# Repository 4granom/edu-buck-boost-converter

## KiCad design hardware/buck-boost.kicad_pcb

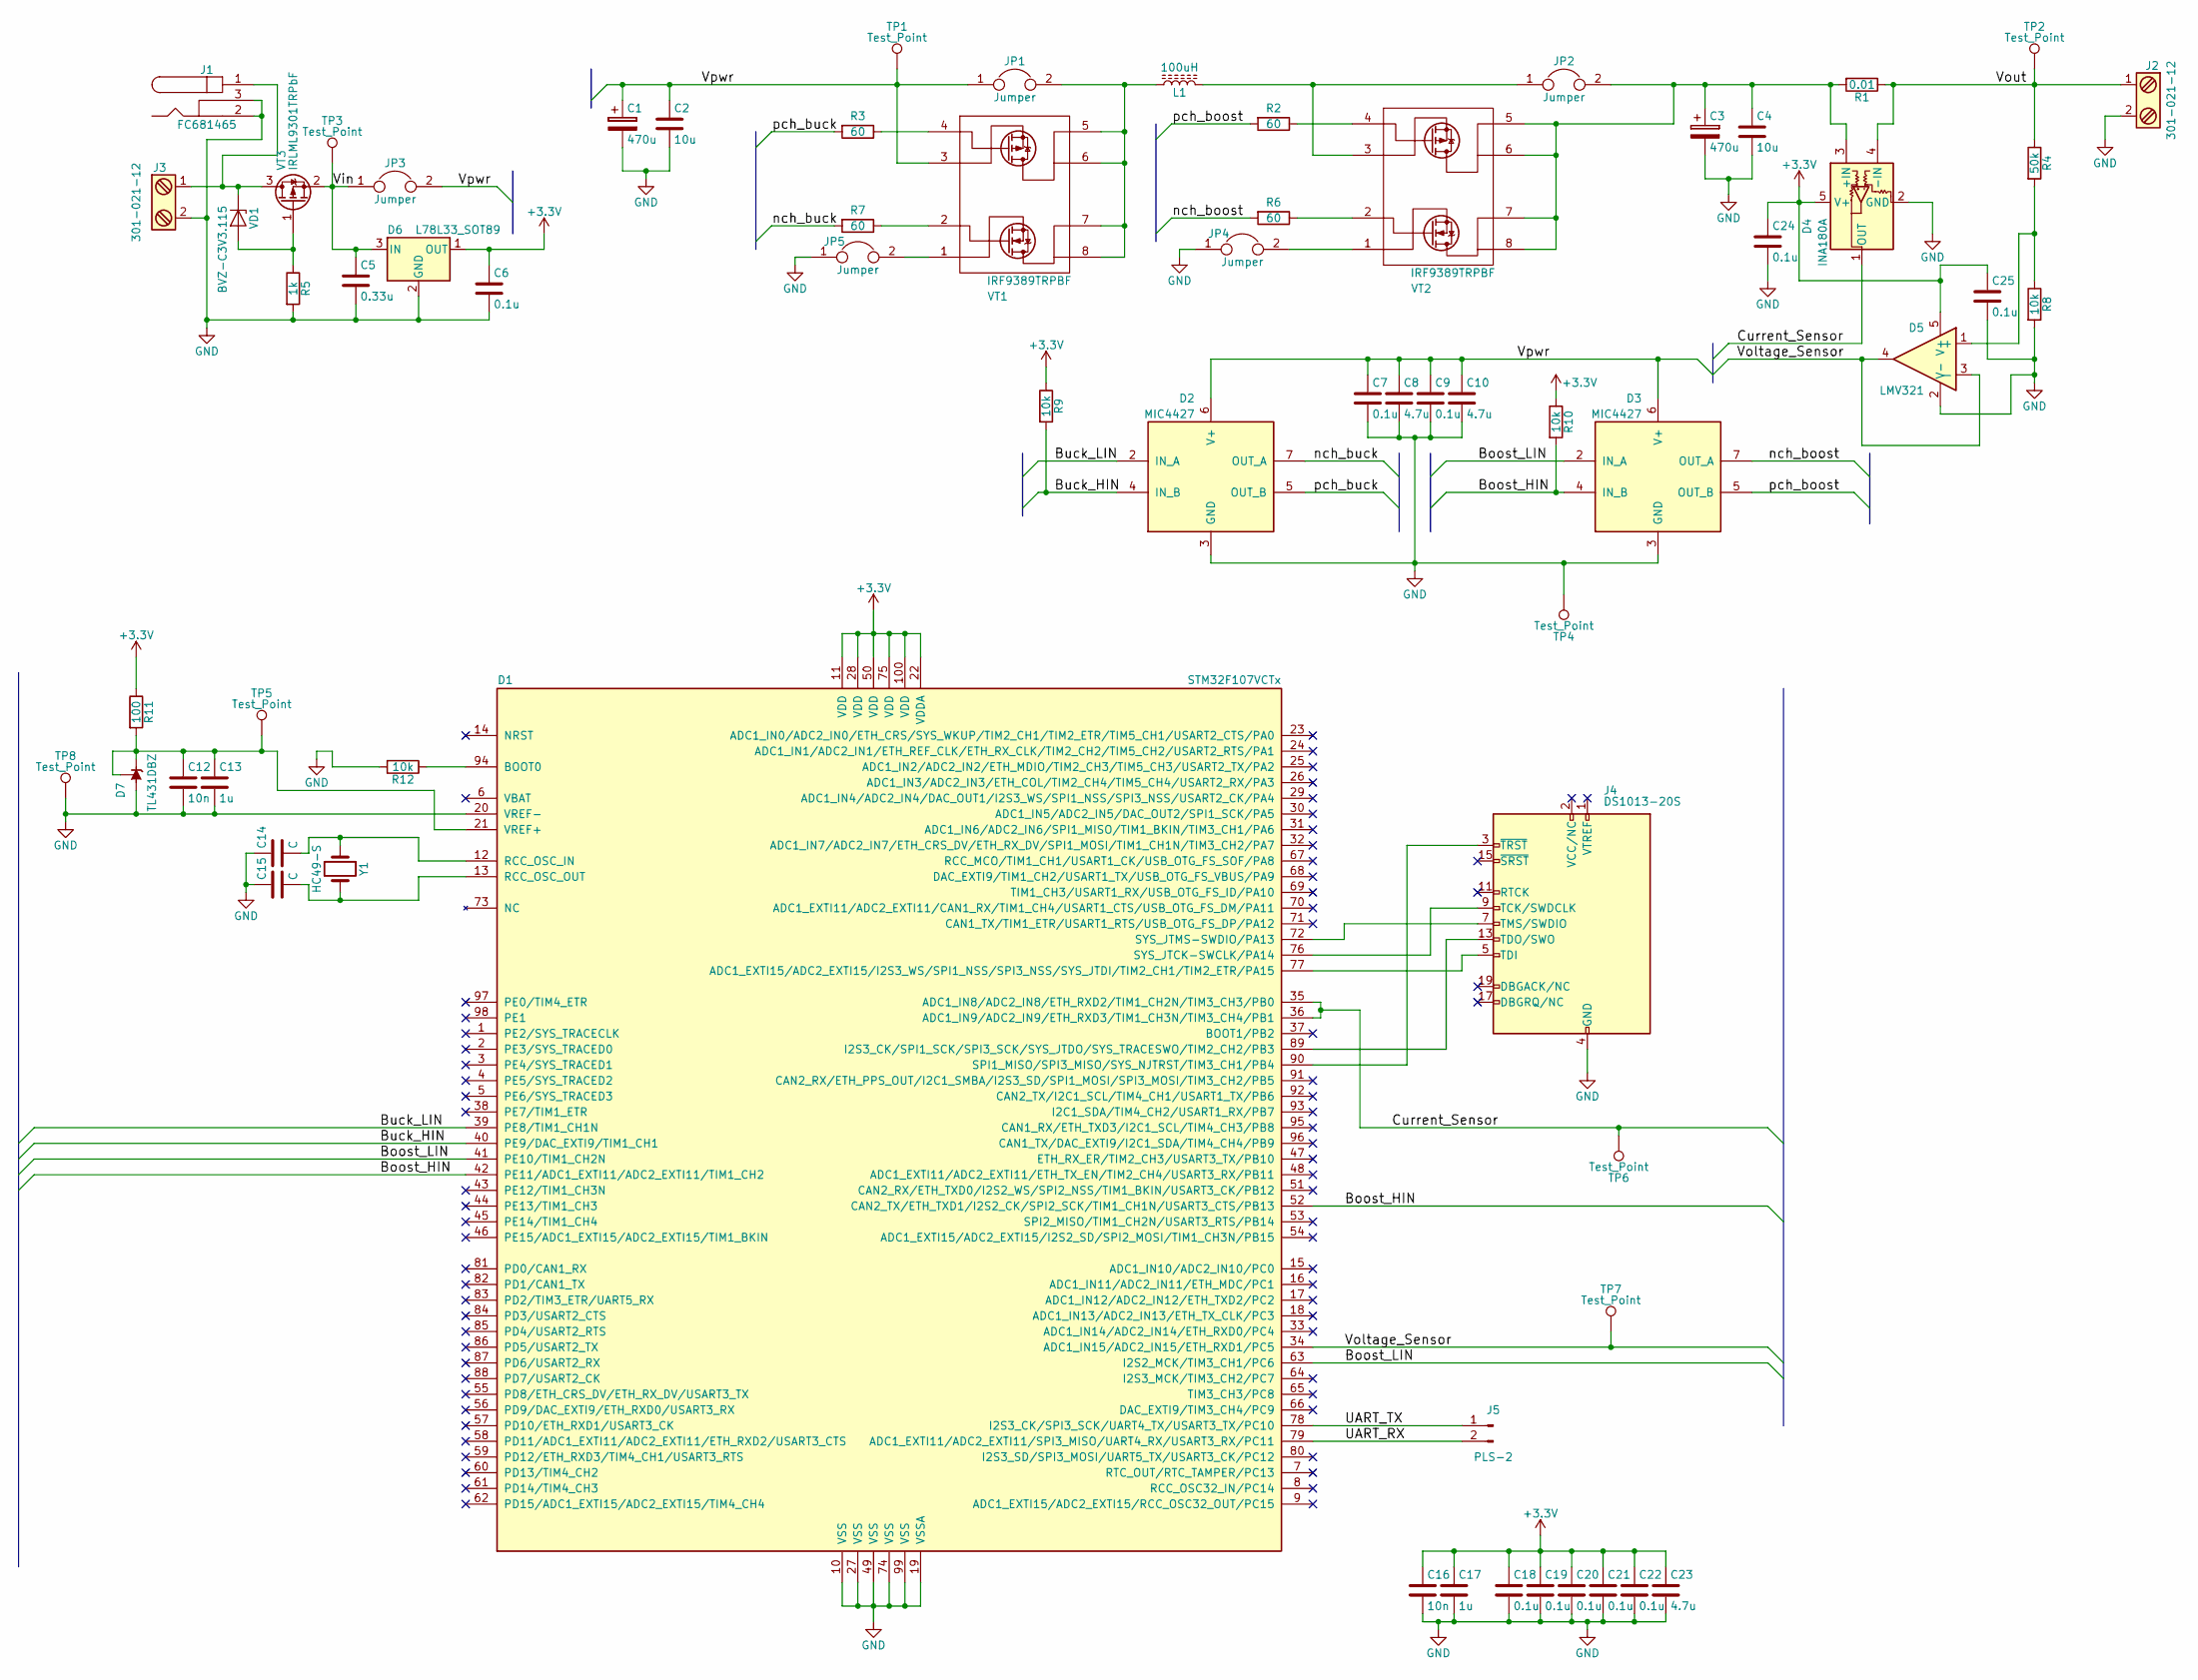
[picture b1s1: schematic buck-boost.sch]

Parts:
C1, C3: 470u; CP_Radial_D10.0mm_P5.00mm
C2, C4: 10u; C_1210_HandSoldering
C5: 0.33u; C_0603_HandSoldering
C6, C7, C9, C18, C19, C20, C21, C22, C24, C25: 0.1u; C_0603_HandSoldering
C8, C10, C23: 4.7u; C_1206_HandSoldering
C12, C16: 10n; C_0603_HandSoldering
C13, C17: 1u; C_0603_HandSoldering
C14, C15: C; C_0603_HandSoldering
D1: STM32F107VCTx; LQFP-100_14x14mm_Pitch0.5mm
D2, D3: MIC4427; SOIC-8_3.9x4.9mm_Pitch1.27mm
D4: INA180A; SOT-23-5_HandSoldering
D5: LMV321; SOT-23-5_HandSoldering
D6: L78L33_SOT89; SOT-89-3_Handsoldering
D7: TL431DBZ; SOT-23
J1: FC681465; BARREL_JACK
J2, J3: 301-021-12; TerminalBlock_Phoenix_MKDS1.5-2pol
J4: DS1013-20S; IDC_Header_Straight_20pins
J5: PLS-2; Pin_Header_Straight_1x02_Pitch2.54mm
JP1, JP2, JP3, JP4, JP5: Jumper; Pin_Header_Straight_1x02_Pitch2.54mm
L1: 100uH; INDUCTOR_Bourns_SDR1307
R1: 0.01; R_1206_HandSoldering
R2, R3, R6, R7: 60; R_0805_HandSoldering
R4: 50k; R_0603_HandSoldering
R5: 1k; R_0603_HandSoldering
R8, R9, R10, R12: 10k; R_0603_HandSoldering
R11: 100; R_0603_HandSoldering
TP1, TP2, TP3, TP5, TP6, TP7: Test_Point; Measurement_Point_Round-SMD-Pad_Small
TP4, TP8: Test_Point; Measurement_Point_Round-TH_Big
VD1: BVZ-C3V3.115; D_1206
VT1, VT2: IRF9389TRPBF; SOIC-8_3.9x4.9mm_Pitch1.27mm
VT3: IRLML9301TRPbF; SOT-23
Y1: HC49-S; Crystal_HC49-U_Vertical

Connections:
+3V3: C6.1, C16.1, C17.1, C18.1, C19.1, C20.1, C21.1, C22.1, C23.1, C24.1, C25.1, D1.11 (VDD), D1.22 (VDDA), D1.28 (VDD), D1.50 (VDD), D1.75 (VDD), D1.100 (VDD), D4.5 (V+), D5.5 (V+), D6.1 (OUT), R9.1, R10.1, R11.1
/Boost_HIN: D1.42 (PE11/ADC1_EXTI11/ADC2_EXTI11/TIM1_CH2), D1.52 (CAN2_TX/ETH_TXD1/I2S2_CK/SPI2_SCK/TIM1_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), D3.4 (IN_B), R10.2
/Boost_LIN: D1.41 (PE10/TIM1_CH2N), D1.63 (I2S2_MCK/TIM3_CH1/PC6), D3.2 (IN_A)
/Buck_HIN: D1.40 (PE9/DAC_EXTI9/TIM1_CH1), D2.4 (IN_B), R9.2
/Buck_LIN: D1.39 (PE8/TIM1_CH1N), D2.2 (IN_A)
/Current_Sensor: D1.35 (ADC1_IN8/ADC2_IN8/ETH_RXD2/TIM1_CH2N/TI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), D1.36 (ADC1_IN9/ADC2_IN9/ETH_RXD3/TIM1_CH3N/TI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), D4.1 (OUT), TP6.1
/UART_RX: D1.79 (ADC1_EXTI11/ADC2_EXTI11/SPI3_MISO/UART4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), J5.2
/UART_TX: D1.78 (I2S3_CK/SPI3_SCK/UART4_TX/USART3_TX/PC10), J5.1
/Vin: C5.1, D6.3 (IN), JP3.1, TP3.1, VT3.2 (S)
/Voltage_Sensor: D1.34 (ADC1_IN15/ADC2_IN15/ETH_RXD1/PC5), D5.3 (-), D5.4, TP7.1
/Vout: D4.4 (-IN), J2.1, R1.1, R4.1, TP2.1
/Vpwr: C1.1, C2.1, C7.1, C8.1, C9.1, C10.1, D2.6 (V+), D3.6 (V+), JP1.1, JP3.2, TP1.1, VT1.3 (S2)
/nch_boost: D3.7 (OUT_A), R6.2
/nch_buck: D2.7 (OUT_A), R7.2
/pch_boost: D3.5 (OUT_B), R2.2
/pch_buck: D2.5 (OUT_B), R3.2
GND: C1.2, C2.2, C3.2, C4.2, C5.2, C6.2, C7.2, C8.2, C9.2, C10.2, C12.2, C13.2, C14.1, C15.1, C16.2, C17.2, C18.2, C19.2, C20.2, C21.2, C22.2, C23.2, C24.2, C25.2, D1.10 (VSS), D1.19 (VSSA), D1.20 (VREF-), D1.27 (VSS), D1.49 (VSS), D1.74 (VSS), D1.99 (VSS), D2.3 (GND), D3.3 (GND), D4.2 (GND), D5.2 (V-), D6.2 (GND), D7.3 (A), J1.2, J1.3, J2.2, J3.2, J4.4 (GND), J4.6 (GND), J4.8 (GND), J4.10 (GND), J4.12 (GND), J4.14 (GND), J4.16 (GND), J4.18 (GND), J4.20 (GND), JP4.1, JP5.1, R5.2, R8.2, R12.2, TP4.1, TP8.1
unnamed: C3.1, C4.1, D4.3 (+IN), JP2.2, R1.2, VT2.5 (D2), VT2.6 (D2), VT2.7 (D1), VT2.8 (D1)
unnamed: C12.1, C13.1, D1.21 (VREF+), D7.1 (K), D7.2 (REF), R11.2, TP5.1
unnamed: C14.2, D1.12 (RCC_OSC_IN), Y1.1
unnamed: C15.2, D1.13 (RCC_OSC_OUT), Y1.2
unnamed: D1.72 (SYS_JTMS-SWDIO/PA13), J4.7 (TMS/SWDIO)
unnamed: D1.76 (SYS_JTCK-SWCLK/PA14), J4.9 (TCK/SWDCLK)
unnamed: D1.77 (ADC1_EXTI15/ADC2_EXTI15/I2S3_WS/SPI1_NS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), J4.5 (TDI)
unnamed: D1.89 (I2S3_CK/SPI1_SCK/SPI3_SCK/SYS_JTDO/SYS_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), J4.13 (TDO/SWO)
unnamed: D1.90 (SPI1_MISO/SPI3_MISO/SYS_NJTRST/TIM3_CH1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), J4.3 (~TRST~)
unnamed: D1.94 (BOOT0), R12.1
unnamed: D5.1 (+), R4.2, R8.1
unnamed: J1.1, J3.1, VD1.1 (K), VT3.3 (D)
unnamed: JP1.2, L1.1, VT1.5 (D2), VT1.6 (D2), VT1.7 (D1), VT1.8 (D1)
unnamed: JP2.1, L1.2, VT2.3 (S2)
unnamed: JP4.2, VT2.1 (S1)
unnamed: JP5.2, VT1.1 (S1)
unnamed: R2.1, VT2.4 (G2)
unnamed: R3.1, VT1.4 (G2)
unnamed: R5.1, VD1.2 (A), VT3.1 (G)
unnamed: R6.1, VT2.2 (G1)
unnamed: R7.1, VT1.2 (G1)

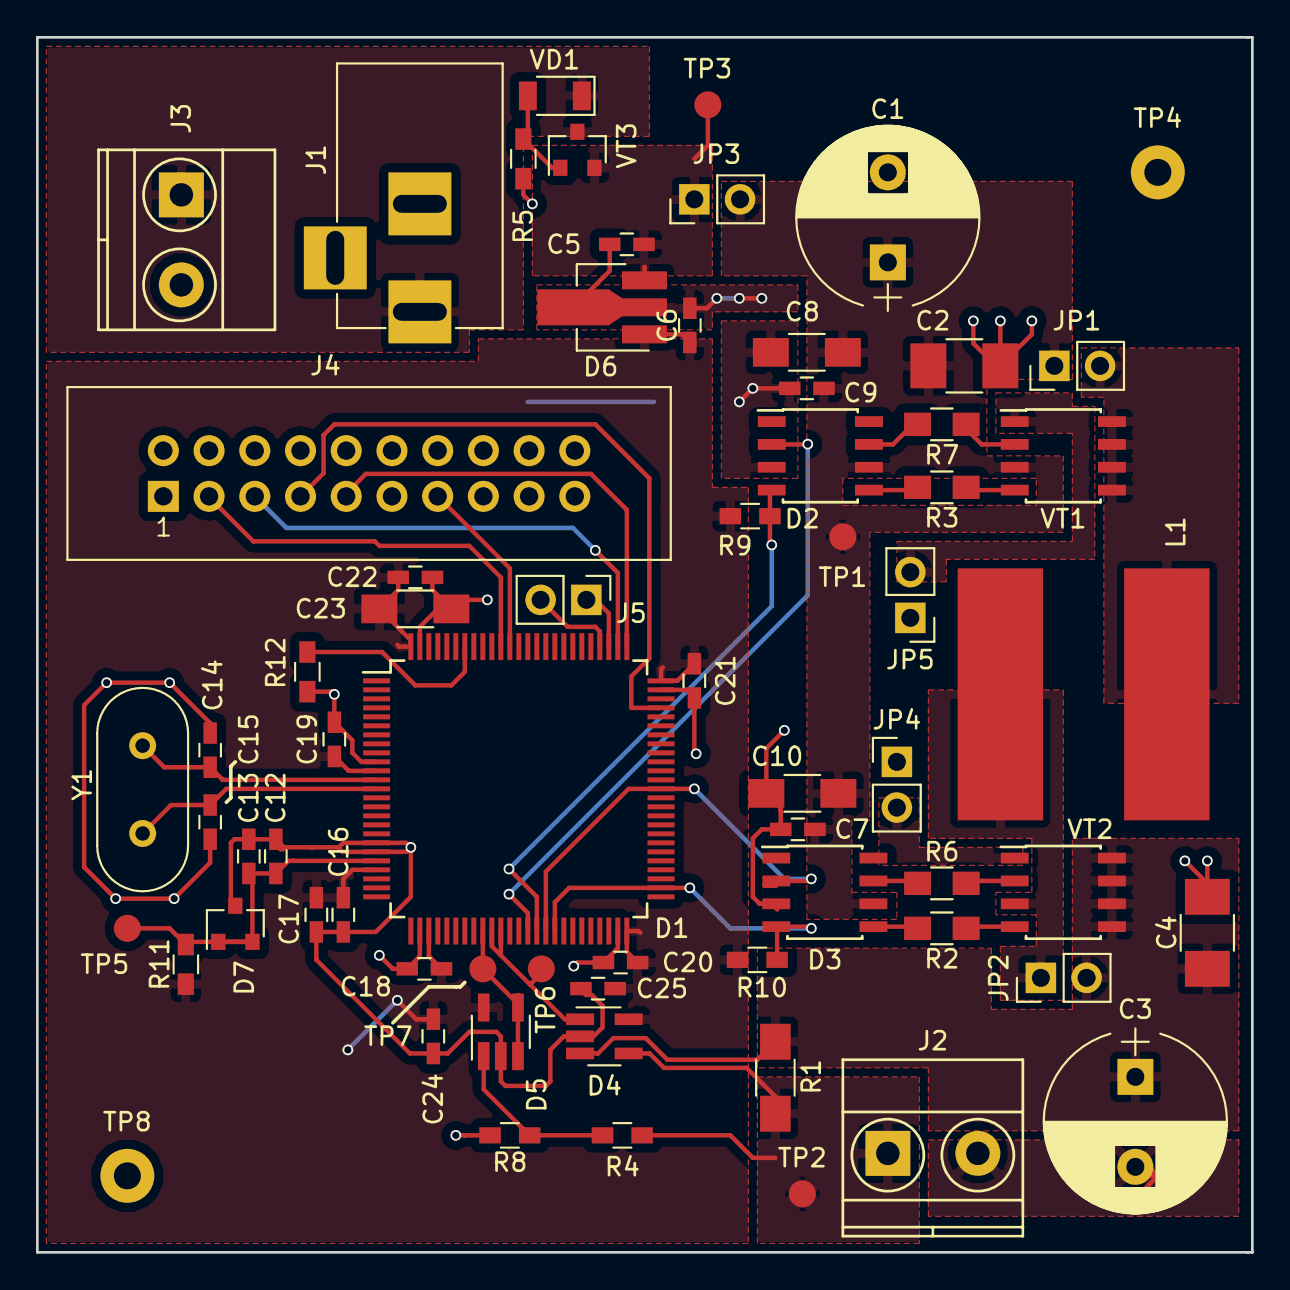
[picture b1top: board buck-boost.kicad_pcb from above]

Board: 2 copper layers, 67.5 x 67.5 mm, 67 parts (0 on the bottom side), 38 nets.

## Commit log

2018-03-09 first commit
    initial schematic
2018-03-10 fix schematic + set footprints
    fix a few issues in schematic and set footprints for all components
2018-03-10 redraw new schematic in pdf
2018-03-11 add pcb to project(first version) and schematic changes
    Schematic
    1. Test points added
    2. Reset button and GNDA deleted
    3. Voltage and Current sensors inputs on MCU (D1) was changed for better PCB design
2018-03-12 change reverse polarity protection from low side to high side
    1. polarity protection schematic changes
    2. new tracing for analog gnd part of pcb (gnda still not in shematic)
